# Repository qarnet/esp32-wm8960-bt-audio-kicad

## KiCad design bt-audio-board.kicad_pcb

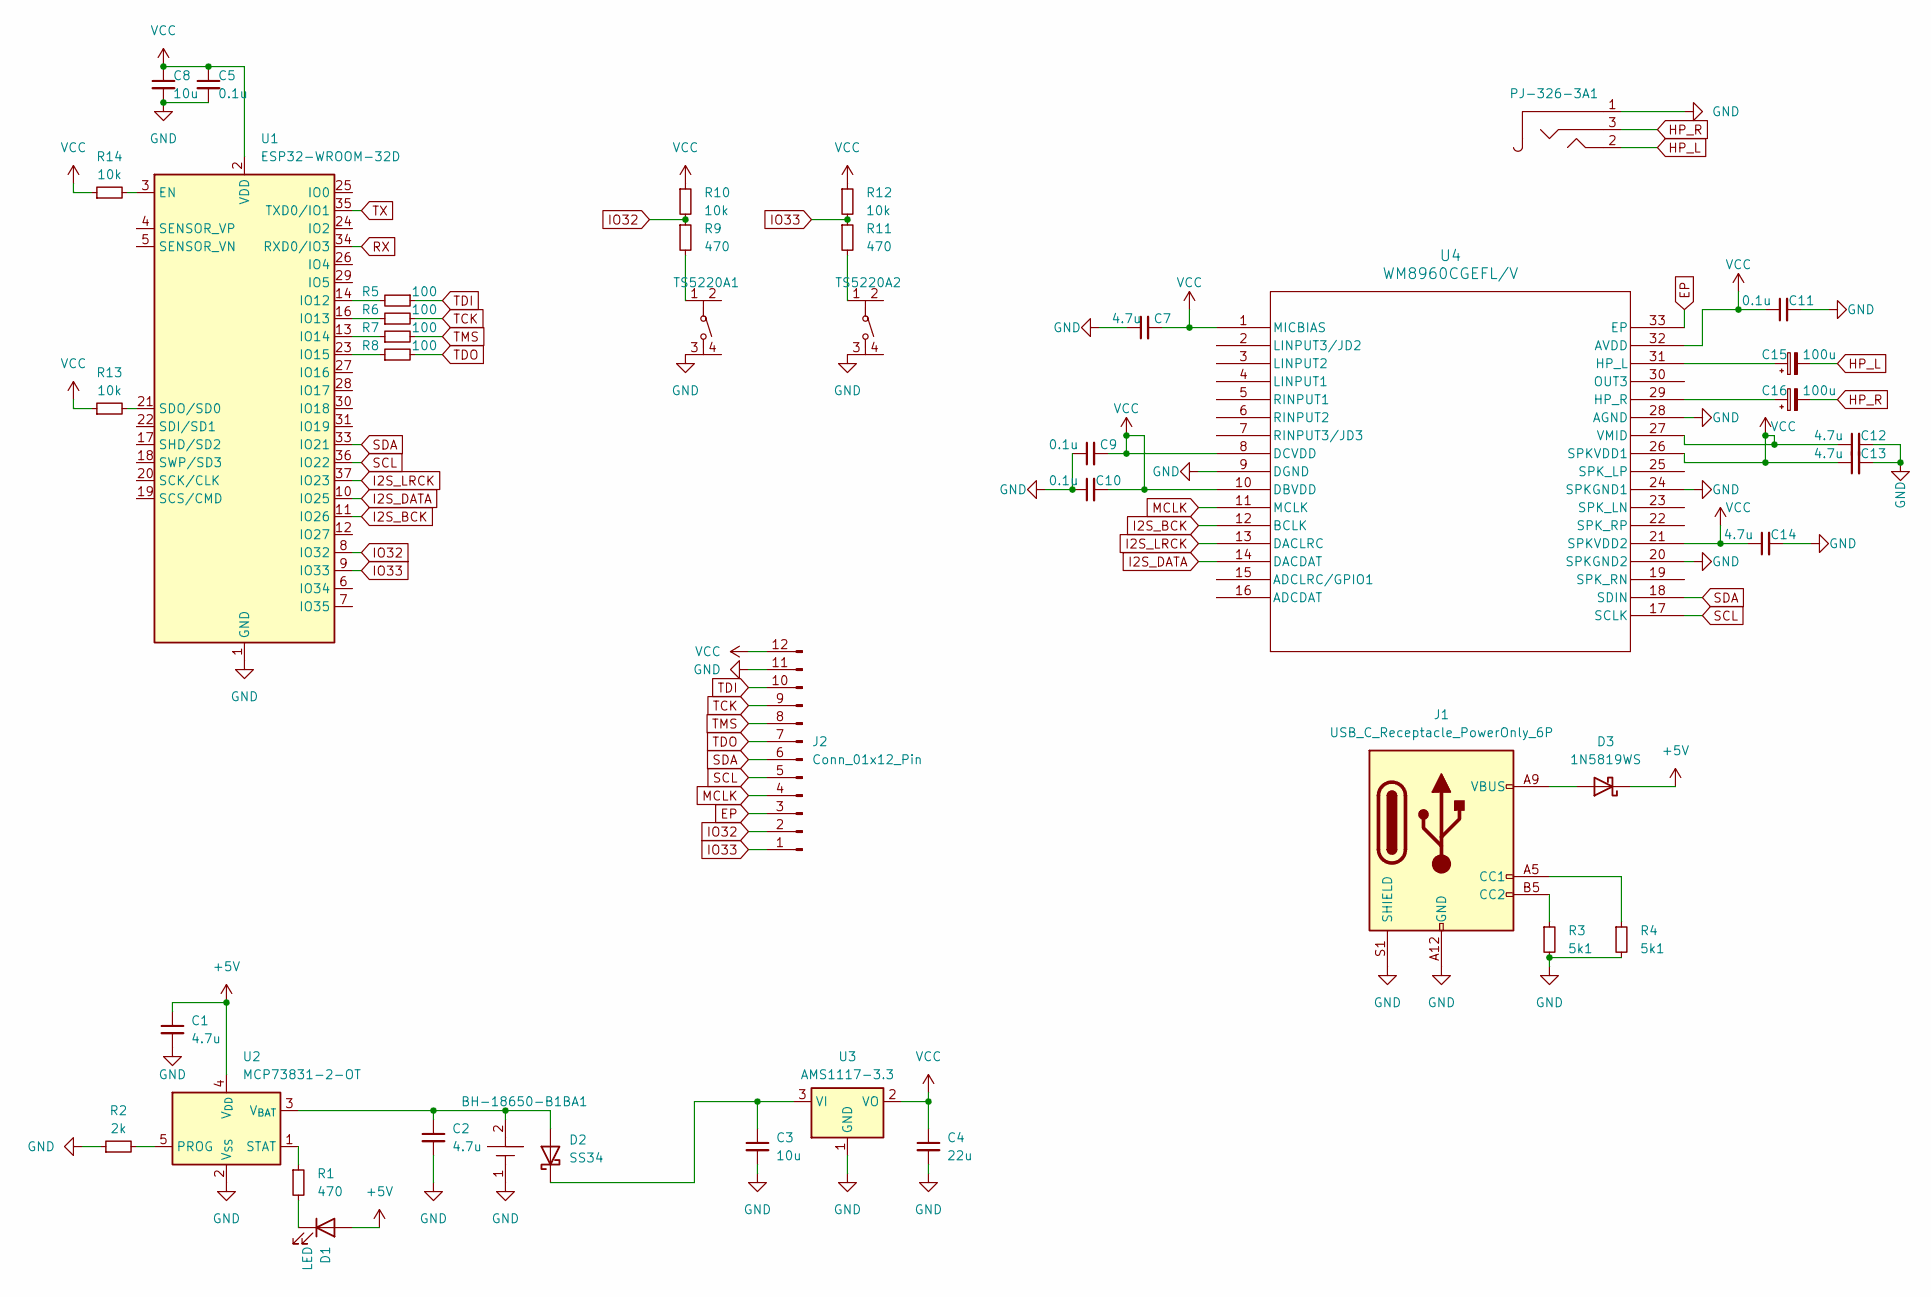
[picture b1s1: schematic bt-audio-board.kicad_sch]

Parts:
BH-18650-B1BA1: BH-18650-B1BA002
C1, C2, C7, C12, C13, C14: 4.7u; C_0603_1608Metric
C3, C8: 10u; C_0603_1608Metric
C4: 22u; C_0603_1608Metric
C5, C9, C10, C11: 0.1u; C_0603_1608Metric
C15, C16: 100u; CP_Elec_6.3x5.4_Nichicon
D1: LED; LED_0603_1608Metric
D2: SS34
D3: 1N5819WS; D_SOD-323
J1: USB_C_Receptacle_PowerOnly_6P
J2: Conn_01x12_Pin; PinHeader_1x12_P2.54mm_Vertical
PJ-326-3A1: PJ-326-3A
R1, R9, R11: 470; R_0603_1608Metric
R2: 2k; R_0603_1608Metric
R3, R4: 5k1; R_0603_1608Metric
R5, R6, R7, R8: 100; R_0603_1608Metric
R10, R12, R13, R14: 10k; R_0603_1608Metric
TS5220A1, TS5220A2: TS5220A
U1: ESP32-WROOM-32D
U2: MCP73831-2-OT; SOT-23-5
U3: AMS1117-3.3; SOT-223-3_TabPin2
U4: WM8960CGEFL/V; WM8960CGEFL/V_CIR

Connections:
+5V: C1.1, D1.2 (A), D3.1 (K), U2.4 (V_{DD})
EP: J2.3, U4.33 (EP)
GND: BH-18650-B1BA1.1, C1.2, C2.2, C3.2, C4.2, C5.2, C7.1, C8.2, C9.1, C10.1, C11.2, C12.2, C13.2, C14.2, J1.A12 (GND), J1.B12 (GND), J1.S1 (SHIELD), J2.11, PJ-326-3A1.1, R2.1, R3.2, R4.2, TS5220A1.3, TS5220A2.3, U1.1 (GND), U1.15 (GND), U1.38 (GND), U1.39 (GND), U2.2 (V_{SS}), U3.1 (GND), U4.9 (DGND), U4.20 (SPKGND2), U4.24 (SPKGND1), U4.28 (AGND)
HP_L: C15.2, PJ-326-3A1.2
HP_R: C16.2, PJ-326-3A1.3
I2S_BCK: U1.11 (IO26), U4.12 (BCLK)
I2S_DATA: U1.10 (IO25), U4.14 (DACDAT)
I2S_LRCK: U1.37 (IO23), U4.13 (DACLRC)
IO32: J2.2, R9.1, R10.2, U1.8 (IO32)
IO33: J2.1, R11.1, R12.2, U1.9 (IO33)
MCLK: J2.4, U4.11 (MCLK)
unnamed: D1.1 (K), R1.2
unnamed: BH-18650-B1BA1.2, C2.1, D2.2 (A), U2.3 (V_{BAT})
unnamed: C3.1, D2.1 (K), U3.3 (VI)
unnamed: D3.2 (A), J1.A9 (VBUS), J1.B9 (VBUS)
unnamed: J1.A5 (CC1), R4.1
unnamed: J1.B5 (CC2), R3.1
unnamed: R9.2, TS5220A1.1
unnamed: R11.2, TS5220A2.1
unnamed: R14.2, U1.3 (EN)
unnamed: R5.2, U1.14 (IO12)
unnamed: R6.1, U1.16 (IO13)
unnamed: R7.1, U1.13 (IO14)
unnamed: R8.1, U1.23 (IO15)
unnamed: R13.2, U1.21 (SDO/SD0)
unnamed: R2.2, U2.5 (PROG)
unnamed: R1.1, U2.1 (STAT)
unnamed: C15.1, U4.31 (HP_L)
unnamed: C16.1, U4.29 (HP_R)
RX: U1.34 (RXD0/IO3)
SCL: J2.5, U1.36 (IO22), U4.17 (SCLK)
SDA: J2.6, U1.33 (IO21), U4.18 (SDIN)
TCK: J2.9, R6.2
TDI: J2.10, R5.1
TDO: J2.7, R8.2
TMS: J2.8, R7.2
TX: U1.35 (TXD0/IO1)
VCC: C4.1, C5.1, C7.2, C8.1, C9.2, C10.2, C11.1, C12.1, C13.1, C14.1, J2.12, R10.1, R12.1, R13.1, R14.1, U1.2 (VDD), U3.2 (VO), U4.1 (MICBIAS), U4.8 (DCVDD), U4.10 (DBVDD), U4.21 (SPKVDD2), U4.26 (SPKVDD1), U4.27 (VMID), U4.32 (AVDD)

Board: 2 copper layers, 42 parts (0 on the bottom side), 36 nets, no tracks yet.

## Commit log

2024-02-02 added files
2024-02-09 schematic finished
